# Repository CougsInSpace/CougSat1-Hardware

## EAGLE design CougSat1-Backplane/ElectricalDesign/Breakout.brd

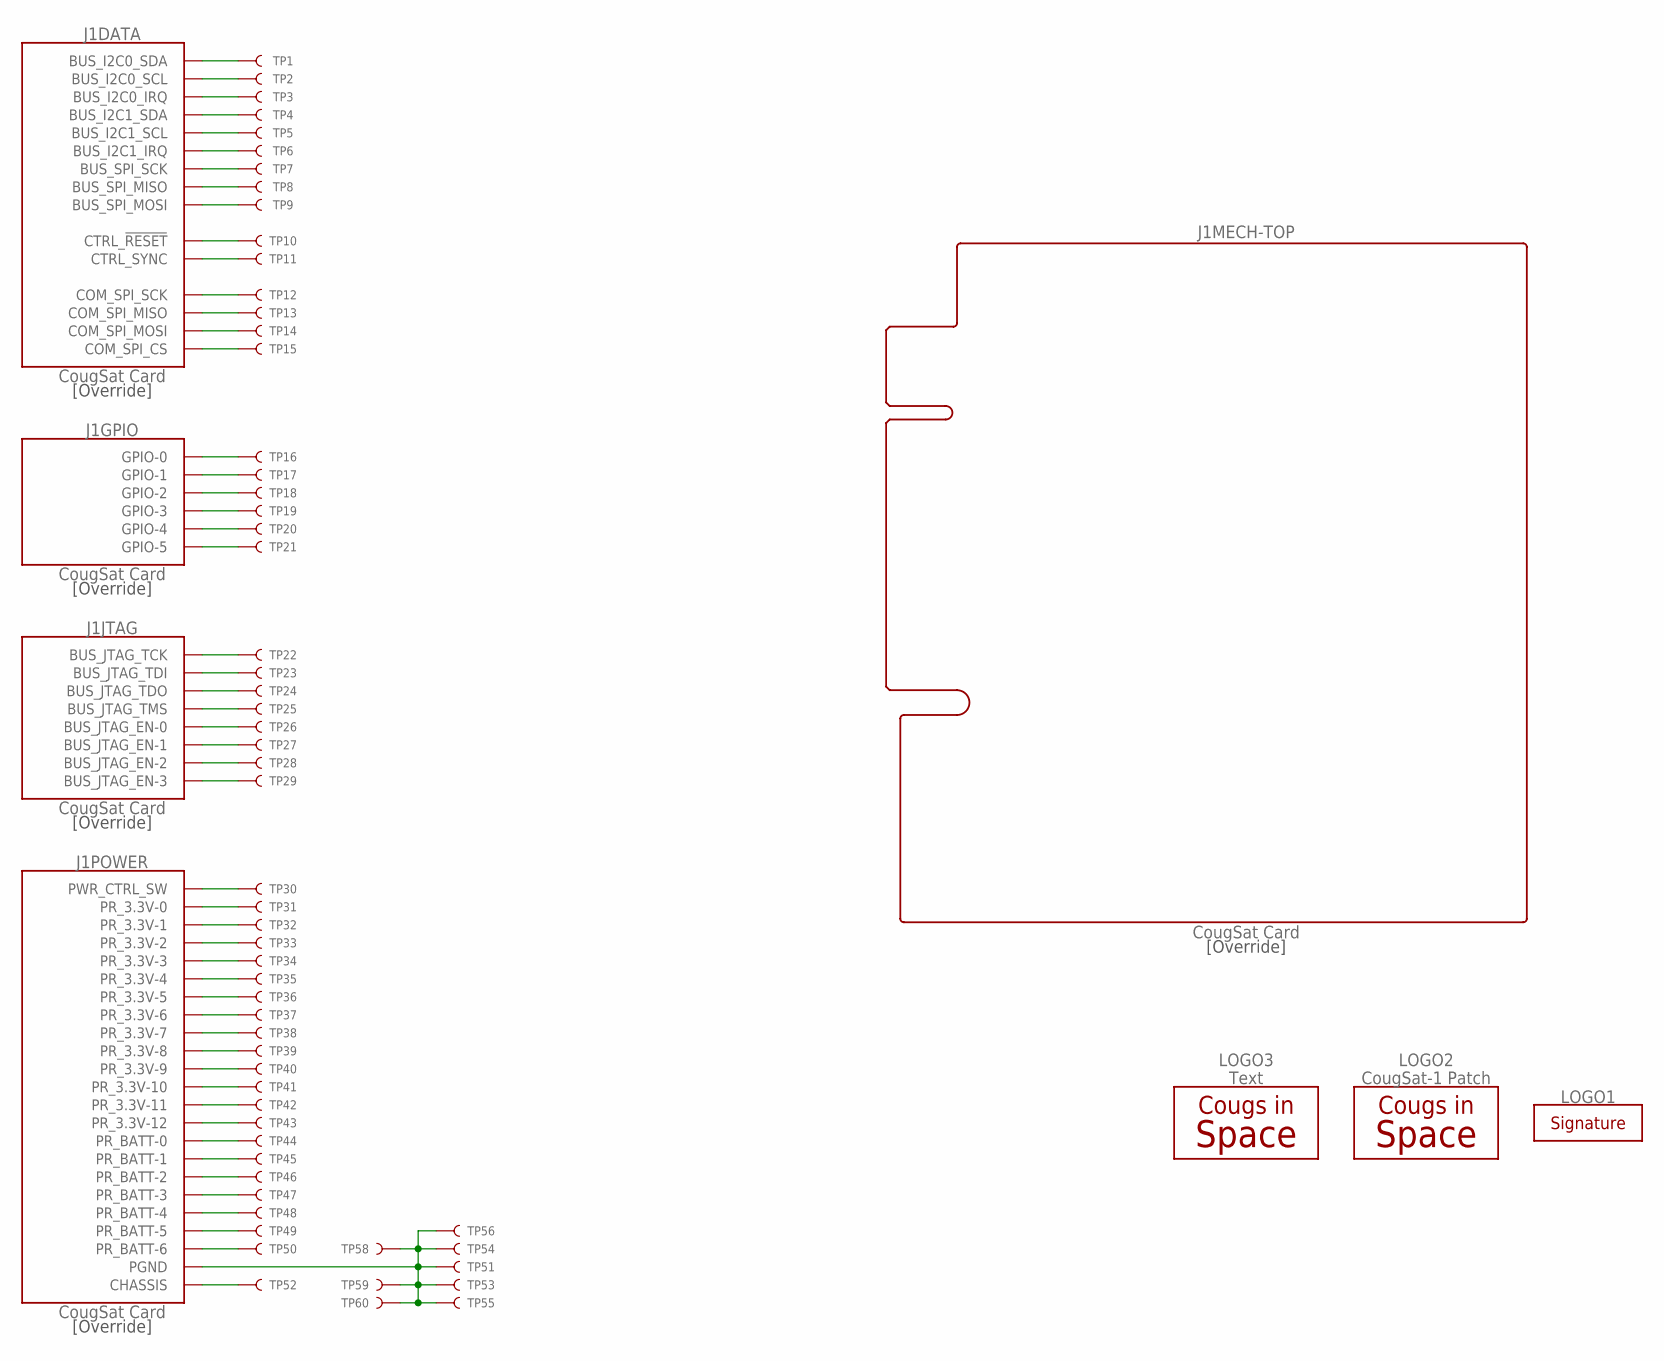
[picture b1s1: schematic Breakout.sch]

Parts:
J1: CougSat Card; CARD-FULL
LOGO1: SIGNATUREHENDRIK; SIGN-HENDRIK
LOGO2: CougSat-1 Patch; CIS-PATCH-1
LOGO3: Text; CIS-TEXT
TP1, TP2, TP3, TP4, TP5, TP6, TP7, TP8, TP9, TP10, TP11, TP12, TP13, TP14, TP15, TP16, TP17, TP18, TP19, TP20, TP21, TP22, TP23, TP24, TP25, TP26, TP27, TP28, TP29, TP30, TP31, TP32, TP33, TP34, TP35, TP36, TP37, TP38, TP39, TP40, TP41, TP42, TP43, TP44, TP45, TP46, TP47, TP48, TP49, TP50, TP51, TP52, TP53, TP54, TP55, TP56, TP58, TP59, TP60: TEST_POINT-THT-1.0; THT-1.0

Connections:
BUS_12C0_IRQ: J1.A45 (BUS_I2C0_IRQ), J1.B45 (BUS_I2C0_IRQ), TP3.1
BUS_12C0_SCL: J1.A44 (BUS_I2C0_SCL), J1.B44 (BUS_I2C0_SCL), TP2.1
BUS_12C0_SDA: J1.A43 (BUS_I2C0_SDA), J1.B43 (BUS_I2C0_SDA), TP1.1
BUS_12C1_IRQ: J1.A32 (BUS_I2C1_IRQ), J1.B32 (BUS_I2C1_IRQ), TP6.1
BUS_12C1_SCL: J1.A31 (BUS_I2C1_SCL), J1.B31 (BUS_I2C1_SCL), TP5.1
BUS_12C1_SDA: J1.A30 (BUS_I2C1_SDA), J1.B30 (BUS_I2C1_SDA), TP4.1
BUS_JTAG_EN-0: J1.B46 (BUS_JTAG_EN-0), TP26.1
BUS_JTAG_EN-1: J1.B47 (BUS_JTAG_EN-1), TP27.1
BUS_JTAG_EN-2: J1.B48 (BUS_JTAG_EN-2), TP28.1
BUS_JTAG_EN-3: J1.B49 (BUS_JTAG_EN-3), TP29.1
BUS_JTAG_TCK: J1.A46 (BUS_JTAG_TCK), TP22.1
BUS_JTAG_TDI: J1.A47 (BUS_JTAG_TDI), TP23.1
BUS_JTAG_TDO: J1.A48 (BUS_JTAG_TDO), TP24.1
BUS_JTAG_TMS: J1.A49 (BUS_JTAG_TMS), TP25.1
BUS_SPI_MISO: J1.A38 (BUS_SPI_MISO), J1.B38 (BUS_SPI_MISO), TP8.1
BUS_SPI_MOSI: J1.A39 (BUS_SPI_MOSI), J1.B39 (BUS_SPI_MOSI), TP9.1
BUS_SPI_SCK: J1.A37 (BUS_SPI_SCK), J1.B37 (BUS_SPI_SCK), TP7.1
CHASSIS: J1.CHASSIS@1 (CHASSIS), J1.CHASSIS@2 (CHASSIS), J1.CHASSIS@3 (CHASSIS), J1.CHASSIS@4 (CHASSIS), TP52.1
COM_SPI_CS: J1.A36 (COM_SPI_CS), J1.B36 (COM_SPI_CS), TP15.1
COM_SPI_MISO: J1.A34 (COM_SPI_MISO), J1.B34 (COM_SPI_MISO), TP13.1
COM_SPI_MOSI: J1.A35 (COM_SPI_MOSI), J1.B35 (COM_SPI_MOSI), TP14.1
COM_SPI_SCK: J1.A33 (COM_SPI_SCK), J1.B33 (COM_SPI_SCK), TP12.1
CTRL_RESET: J1.A41 (CTRL_!RESET), J1.B41 (CTRL_!RESET), TP10.1
CTRL_SYNC: J1.A42 (CTRL_SYNC), J1.B42 (CTRL_SYNC), TP11.1
GPIO-0: J1.A24 (GPIO-0), TP16.1
GPIO-1: J1.A25 (GPIO-1), TP17.1
GPIO-2: J1.A26 (GPIO-2), TP18.1
GPIO-3: J1.A27 (GPIO-3), TP19.1
GPIO-4: J1.A28 (GPIO-4), TP20.1
GPIO-5: J1.A29 (GPIO-5), TP21.1
PGND: J1.A21 (PGND), J1.A22 (PGND), J1.A23 (PGND), J1.B21 (PGND), J1.B22 (PGND), J1.B23 (PGND), J1.B24 (PGND), J1.B25 (PGND), J1.B26 (PGND), J1.B27 (PGND), J1.B28 (PGND), J1.B29 (PGND), TP51.1, TP53.1, TP54.1, TP55.1, TP56.1, TP58.1, TP59.1, TP60.1
PR_3.3V-0: J1.A1 (PR_3.3V-0), J1.B1 (PR_3.3V-0), TP31.1
PR_3.3V-1: J1.A2 (PR_3.3V-1), J1.B2 (PR_3.3V-1), TP32.1
PR_3.3V-2: J1.A3 (PR_3.3V-2), J1.B3 (PR_3.3V-2), TP33.1
PR_3.3V-3: J1.A4 (PR_3.3V-3), J1.B4 (PR_3.3V-3), TP34.1
PR_3.3V-4: J1.A5 (PR_3.3V-4), J1.B5 (PR_3.3V-4), TP35.1
PR_3.3V-5: J1.A6 (PR_3.3V-5), J1.B6 (PR_3.3V-5), TP36.1
PR_3.3V-6: J1.A7 (PR_3.3V-6), J1.B7 (PR_3.3V-6), TP37.1
PR_3.3V-7: J1.A8 (PR_3.3V-7), J1.B8 (PR_3.3V-7), TP38.1
PR_3.3V-8: J1.A9 (PR_3.3V-8), J1.B9 (PR_3.3V-8), TP39.1
PR_3.3V-9: J1.A10 (PR_3.3V-9), J1.B10 (PR_3.3V-9), TP40.1
PR_3.3V-10: J1.A11 (PR_3.3V-10), J1.B11 (PR_3.3V-10), TP41.1
PR_3.3V-11: J1.A12 (PR_3.3V-11), J1.B12 (PR_3.3V-11), TP42.1
PR_3.3V-12: J1.A13 (PR_3.3V-12), J1.B13 (PR_3.3V-12), TP43.1
PR_BATT-0: J1.A14 (PR_BATT-0), J1.B14 (PR_BATT-0), TP44.1
PR_BATT-1: J1.A15 (PR_BATT-1), J1.B15 (PR_BATT-1), TP45.1
PR_BATT-2: J1.A16 (PR_BATT-2), J1.B16 (PR_BATT-2), TP46.1
PR_BATT-3: J1.A17 (PR_BATT-3), J1.B17 (PR_BATT-3), TP47.1
PR_BATT-4: J1.A18 (PR_BATT-4), J1.B18 (PR_BATT-4), TP48.1
PR_BATT-5: J1.A19 (PR_BATT-5), J1.B19 (PR_BATT-5), TP49.1
PR_BATT-6: J1.A20 (PR_BATT-6), J1.B20 (PR_BATT-6), TP50.1
PWR_CTRL_SW: J1.A40 (PWR_CTRL_SW), J1.B40 (PWR_CTRL_SW), TP30.1

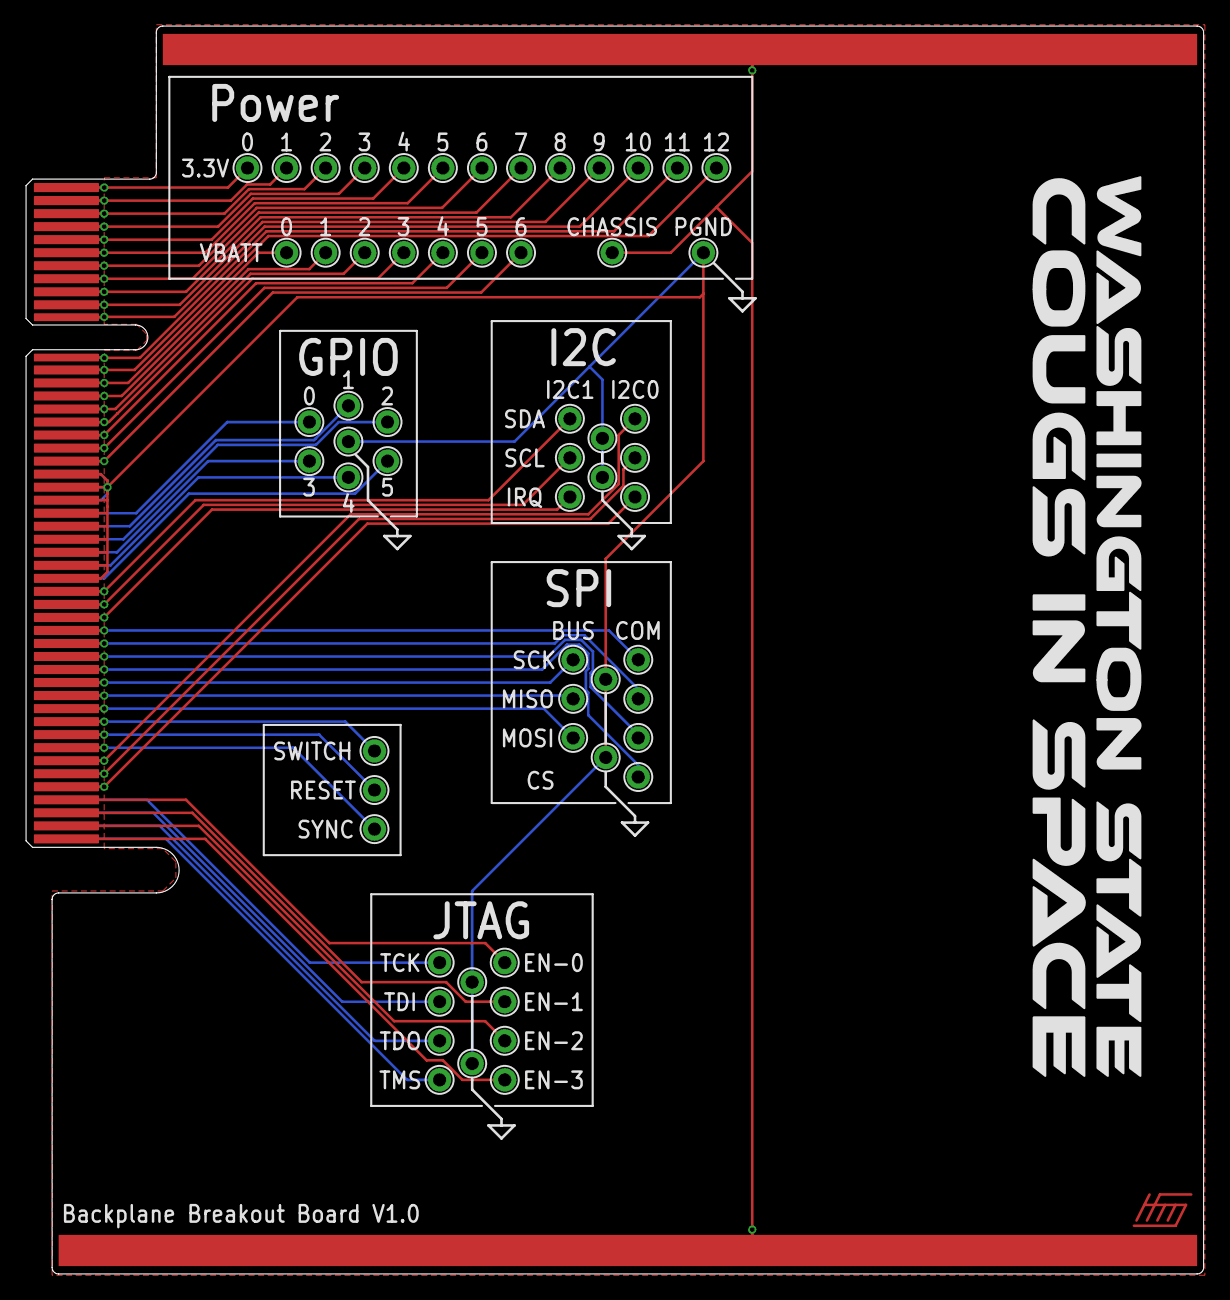
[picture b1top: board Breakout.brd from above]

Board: 2 copper layers, 90.4 x 95.8 mm, 63 parts (1 on the bottom side), 52 nets.

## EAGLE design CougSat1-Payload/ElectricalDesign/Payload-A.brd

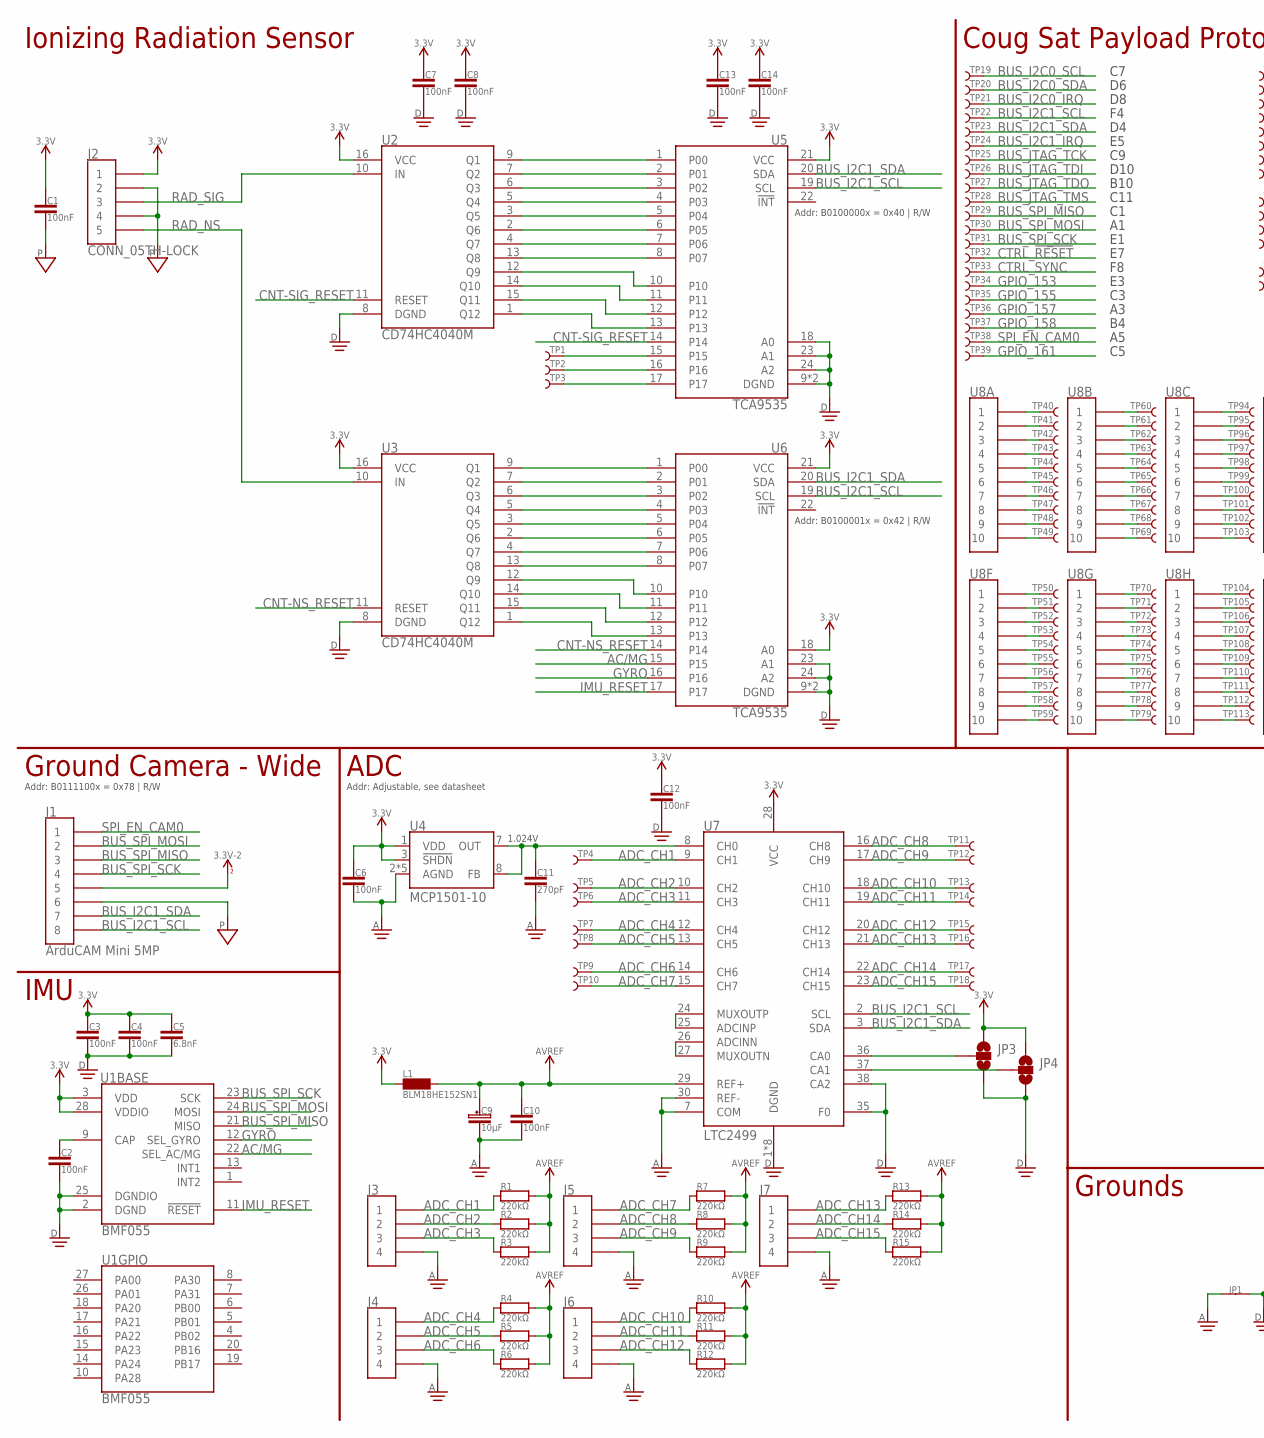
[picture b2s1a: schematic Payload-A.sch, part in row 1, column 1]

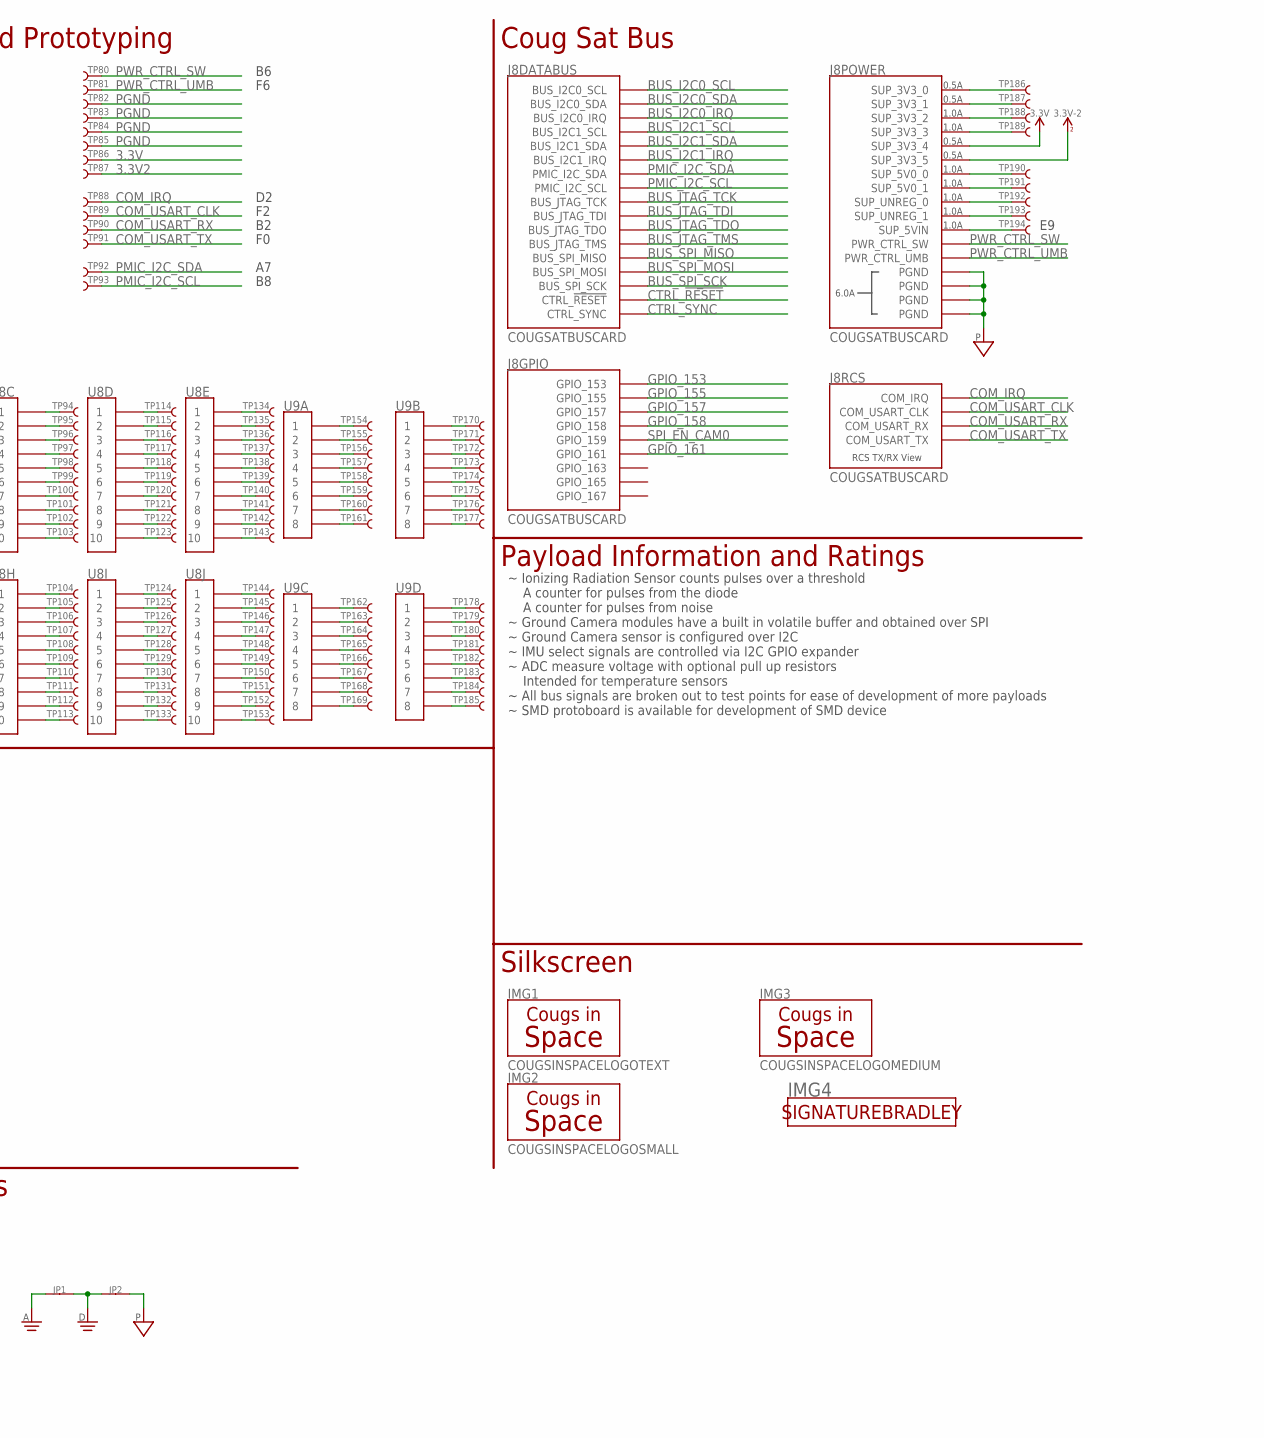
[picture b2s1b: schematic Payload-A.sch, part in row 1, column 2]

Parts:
C1, C2, C3, C4, C6, C7, C8, C10, C13, C14: 100nF; 1608
C5: 6.8nF; 1608
C9: 10µF; 4028-POL
C11: 270pF; 1608
C12: 100nF; 3216
IMG1: COUGSINSPACELOGOTEXT; COUGSINSPACETEXT
IMG2: COUGSINSPACELOGOSMALL; COUGSINSPACELOGO_SMALL
IMG3: COUGSINSPACELOGOMEDIUM; COUGSINSPACELOGO_MEDIUM
IMG4: SIGNATUREBRADLEY; SIGNATURE-BRADLEY
J1: ArduCAM Mini 5MP; 1X08_LOCK
J2: CONN_05TH-LOCK; 1X05_LOCK
J3, J4, J5, J6, J7: CONN_04PICOLOCK1.5MM; 1X04_PICOLOCK1.5MM
J8: COUGSATBUSCARD; COUGSATBUS_MALE-SODIMM
JP1, JP2: SHORTCIRCUIT1608JUMPER; 1608
JP3, JP4: JUMPER-SMT_3_NO_SILK; SMT-JUMPER_3_NO_SILK
L1: BLM18HE152SN1; 1608
R1, R2, R3, R4, R5, R6, R7, R8, R9, R10, R11, R12, R13, R14, R15: 220kΩ; 1608
TP1, TP2, TP3, TP4, TP5, TP6, TP7, TP8, TP9, TP10, TP11, TP12, TP13, TP14, TP15, TP16, TP17, TP18, TP19, TP20, TP21, TP22, TP23, TP24, TP25, TP26, TP27, TP28, TP29, TP30, TP31, TP32, TP33, TP34, TP35, TP36, TP37, TP38, TP39, TP80, TP81, TP82, TP83, TP84, TP85, TP86, TP87, TP88, TP89, TP90, TP91, TP92, TP93, TP186, TP187, TP188, TP189, TP190, TP191, TP192, TP193, TP194: TEST-POINT1.25MM; PAD1.25X1.25
TP40, TP41, TP42, TP43, TP44, TP45, TP46, TP47, TP48, TP49, TP50, TP51, TP52, TP53, TP54, TP55, TP56, TP57, TP58, TP59, TP60, TP61, TP62, TP63, TP64, TP65, TP66, TP67, TP68, TP69, TP70, TP71, TP72, TP73, TP74, TP75, TP76, TP77, TP78, TP79, TP94, TP95, TP96, TP97, TP98, TP99, TP100, TP101, TP102, TP103, TP104, TP105, TP106, TP107, TP108, TP109, TP110, TP111, TP112, TP113, TP114, TP115, TP116, TP117, TP118, TP119, TP120, TP121, TP122, TP123, TP124, TP125, TP126, TP127, TP128, TP129, TP130, TP131, TP132, TP133, TP134, TP135, TP136, TP137, TP138, TP139, TP140, TP141, TP142, TP143, TP144, TP145, TP146, TP147, TP148, TP149, TP150, TP151, TP152, TP153, TP154, TP155, TP156, TP157, TP158, TP159, TP160, TP161, TP162, TP163, TP164, TP165, TP166, TP167, TP168, TP169, TP170, TP171, TP172, TP173, TP174, TP175, TP176, TP177, TP178, TP179, TP180, TP181, TP182, TP183, TP184, TP185: TEST-POINT1MM; PAD1X1
U1: BMF055; LGA28-4X5MM
U2, U3: CD74HC4040M; SO16
U4: MCP1501-10; WDFN8-2X2
U5, U6: TCA9535; QFN24-4X4
U7: LTC2499; QFN38-5X7
U8: PROTOBOARD-100SMD0.5MM; PROTOBOARD-SMD0.5MM
U9: PROTOBOARD-32SOIC; PROTOBOARD-SOIC

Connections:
3.3V: C1.1, C3.1, C4.1, C5.1, C6.1, C7.1, C8.1, C12.1, C13.1, C14.1, J2.1, J8.42 (SUP_3V3_4), J8.44 (SUP_3V3_4), J8.46 (SUP_3V3_4), J8.48 (SUP_3V3_4), J8.50 (SUP_3V3_4), JP3.1, JP4.1, L1.2, TP86.1, U1.3 (VDD), U1.28 (VDDIO), U2.16 (VCC), U3.16 (VCC), U4.1 (VDD), U4.3 (!SHDN), U5.21 (VCC), U6.18 (A0), U6.21 (VCC), U7.28 (VCC)
3.3V2: J1.5, J8.52 (SUP_3V3_5), J8.54 (SUP_3V3_5), J8.56 (SUP_3V3_5), J8.58 (SUP_3V3_5), J8.60 (SUP_3V3_5), TP87.1
AC/MG: U1.22 (SEL_AC/MG), U6.15
ADCS_ADCINP: U7.24 (MUXOUTP), U7.25 (ADCINP)
ADCS_ADCSINN: U7.26 (ADCINN), U7.27 (MUXOUTN)
ADC_CA0: JP3.2, U7.36 (CA0)
ADC_CA1: JP4.2, U7.37 (CA1)
ADC_CH1: J3.1, R1.1, TP4.1, U7.9 (CH1)
ADC_CH2: J3.2, R2.1, TP5.1, U7.10 (CH2)
ADC_CH3: J3.3, R3.1, TP6.1, U7.11 (CH3)
ADC_CH4: J4.1, R4.1, TP7.1, U7.12 (CH4)
ADC_CH5: J4.2, R5.1, TP8.1, U7.13 (CH5)
ADC_CH6: J4.3, R6.1, TP9.1, U7.14 (CH6)
ADC_CH7: J5.1, R7.1, TP10.1, U7.15 (CH7)
ADC_CH8: J5.2, R8.1, TP11.1, U7.16 (CH8)
ADC_CH9: J5.3, R9.1, TP12.1, U7.17 (CH9)
ADC_CH10: J6.1, R10.1, TP13.1, U7.18 (CH10)
ADC_CH11: J6.2, R11.1, TP14.1, U7.19 (CH11)
ADC_CH12: J6.3, R12.1, TP15.1, U7.20 (CH12)
ADC_CH13: J7.1, R13.1, TP16.1, U7.21 (CH13)
ADC_CH14: J7.2, R14.1, TP17.1, U7.22 (CH14)
ADC_CH15: J7.3, R15.1, TP18.1, U7.23 (CH15)
ADC_VREF_ICOUT: C11.1, U4.7 (OUT), U4.8 (FB), U7.8 (CH0)
AGND: C6.2, C9.C, C10.2, C11.2, J3.4, J4.4, J5.4, J6.4, J7.4, JP1.1, U4.2 (AGND), U4.4 (AGND), U4.5 (AGND), U4.6 (AGND), U4.PAD (AGND), U7.7 (COM), U7.30 (REF-)
AVREF: C9.A, C10.1, L1.1, R1.2, R2.2, R3.2, R4.2, R5.2, R6.2, R7.2, R8.2, R9.2, R10.2, R11.2, R12.2, R13.2, R14.2, R15.2, U7.29 (REF+)
BUS_I2C0_IRQ: J8.177 (BUS_I2C0_IRQ), J8.179 (BUS_I2C0_IRQ), TP21.1
BUS_I2C0_SCL: J8.173 (BUS_I2C0_SCL), J8.175 (BUS_I2C0_SCL), TP19.1
BUS_I2C0_SDA: J8.169 (BUS_I2C0_SDA), J8.171 (BUS_I2C0_SDA), TP20.1
BUS_I2C1_IRQ: J8.164 (BUS_I2C1_IRQ), TP24.1
BUS_I2C1_SCL: J1.8, J8.160 (BUS_I2C1_SCL), TP22.1, U5.19 (SCL), U6.19 (SCL), U7.2 (SCL)
BUS_I2C1_SDA: J1.7, J8.162 (BUS_I2C1_SDA), TP23.1, U5.20 (SDA), U6.20 (SDA), U7.3 (SDA)
BUS_JTAG_TCK: J8.185 (BUS_JTAG_TCK), J8.187 (BUS_JTAG_TCK), TP25.1
BUS_JTAG_TDI: J8.189 (BUS_JTAG_TDI), J8.191 (BUS_JTAG_TDI), TP26.1
BUS_JTAG_TDO: J8.193 (BUS_JTAG_TDO), J8.195 (BUS_JTAG_TDO), TP27.1
BUS_JTAG_TMS: J8.197 (BUS_JTAG_TMS), J8.199 (BUS_JTAG_TMS), TP28.1
BUS_SPI_MISO: J1.3, J8.145 (BUS_SPI_MISO), J8.147 (BUS_SPI_MISO), TP29.1, U1.21 (MISO)
BUS_SPI_MOSI: J1.2, J8.149 (BUS_SPI_MOSI), J8.151 (BUS_SPI_MOSI), TP30.1, U1.24 (MOSI)
BUS_SPI_SCK: J1.4, J8.141 (BUS_SPI_SCK), J8.143 (BUS_SPI_SCK), TP31.1, U1.23 (SCK)
CNT-NS_1: U3.9 (Q1), U6.1 (P00)
CNT-NS_2: U3.7 (Q2), U6.2 (P01)
CNT-NS_3: U3.6 (Q3), U6.3 (P02)
CNT-NS_4: U3.5 (Q4), U6.4 (P03)
CNT-NS_5: U3.3 (Q5), U6.5 (P04)
CNT-NS_6: U3.2 (Q6), U6.6 (P05)
CNT-NS_7: U3.4 (Q7), U6.7 (P06)
CNT-NS_8: U3.13 (Q8), U6.8 (P07)
CNT-NS_9: U3.12 (Q9), U6.10
CNT-NS_10: U3.14 (Q10), U6.11
CNT-NS_11: U3.15 (Q11), U6.12
CNT-NS_12: U3.1 (Q12), U6.13
CNT-NS_RESET: U3.11 (RESET), U6.14
CNT-SIG_1: U2.9 (Q1), U5.1 (P00)
CNT-SIG_2: U2.7 (Q2), U5.2 (P01)
CNT-SIG_3: U2.6 (Q3), U5.3 (P02)
CNT-SIG_4: U2.5 (Q4), U5.4 (P03)
CNT-SIG_5: U2.3 (Q5), U5.5 (P04)
CNT-SIG_6: U2.2 (Q6), U5.6 (P05)
CNT-SIG_7: U2.4 (Q7), U5.7 (P06)
CNT-SIG_8: U2.13 (Q8), U5.8 (P07)
CNT-SIG_9: U2.12 (Q9), U5.10
CNT-SIG_10: U2.14 (Q10), U5.11
CNT-SIG_11: U2.15 (Q11), U5.12
CNT-SIG_12: U2.1 (Q12), U5.13
CNT-SIG_RESET: U2.11 (RESET), U5.14
COM_IRQ: J8.154 (COM_IRQ), J8.156 (COM_IRQ), TP88.1
COM_USART_CLK: J8.150 (COM_USART_CLK), J8.152 (COM_USART_CLK), TP89.1
COM_USART_RX: J8.146 (COM_USART_RX), J8.148 (COM_USART_RX), TP90.1
COM_USART_TX: J8.142 (COM_USART_TX), J8.144 (COM_USART_TX), TP91.1
CTRL_!RESET: J8.174 (CTRL_!RESET), J8.176 (CTRL_!RESET), TP32.1
CTRL_SYNC: J8.178 (CTRL_SYNC), J8.180 (CTRL_SYNC), TP33.1
DGND: C2.2, C3.2, C4.2, C5.2, C7.2, C8.2, C12.2, C13.2, C14.2, JP1.2, JP2.1, JP3.3, JP4.3, U1.2 (DGND), U1.25 (DGNDIO), U2.8 (DGND), U3.8 (DGND), U5.9 (DGND), U5.18 (A0), U5.23 (A1), U5.24 (A2), U5.PAD (DGND), U6.9 (DGND), U6.23 (A1), U6.24 (A2), U6.PAD (DGND), U7.1 (DGND), U7.4 (DGND), U7.6 (DGND), U7.31 (DGND), U7.32 (DGND), U7.33 (DGND), U7.34 (DGND), U7.35 (F0), U7.38 (CA2), U7.PAD (DGND)
GPIO_153: J8.153 (GPIO_153), TP34.1
GPIO_155: J8.155 (GPIO_155), TP35.1
GPIO_157: J8.157 (GPIO_157), TP36.1
GPIO_158: J8.158 (GPIO_158), TP37.1
GPIO_161: J8.161 (GPIO_161), TP39.1
GPIO_P15: TP1.1, U5.15
GPIO_P16: TP2.1, U5.16
GPIO_P17: TP3.1, U5.17
GYRO: U1.12 (SEL_GYRO), U6.16
IMU2_CAP: C2.1, U1.9 (CAP)
IMU_RESET: U1.11 (!RESET), U6.17
PGND: C1.2, J1.6, J2.2, J2.4, J8.1 (PGND), J8.3 (PGND), J8.5 (PGND), J8.7 (PGND), J8.9 (PGND), J8.11 (PGND), J8.13 (PGND), J8.15 (PGND), J8.17 (PGND), J8.19 (PGND), J8.41 (PGND), J8.43 (PGND), J8.45 (PGND), J8.47 (PGND), J8.49 (PGND), J8.51 (PGND), J8.53 (PGND), J8.55 (PGND), J8.57 (PGND), J8.59 (PGND), J8.61 (PGND), J8.63 (PGND), J8.65 (PGND), J8.67 (PGND), J8.69 (PGND), J8.82 (PGND), J8.84 (PGND), J8.86 (PGND), J8.88 (PGND), J8.90 (PGND), J8.92 (PGND), J8.94 (PGND), J8.96 (PGND), J8.98 (PGND), J8.100 (PGND), J8.102 (PGND), J8.104 (PGND), J8.106 (PGND), J8.108 (PGND), J8.110 (PGND), J8.112 (PGND), J8.114 (PGND), J8.116 (PGND), J8.118 (PGND), J8.120 (PGND), J8.122 (PGND), J8.124 (PGND), J8.126 (PGND), J8.128 (PGND), J8.130 (PGND), J8.131 (PGND), J8.132 (PGND), J8.133 (PGND), J8.134 (PGND), J8.135 (PGND), J8.136 (PGND), J8.137 (PGND), J8.138 (PGND), J8.139 (PGND), J8.140 (PGND), JP2.2, TP82.1, TP83.1, TP84.1, TP85.1
PMIC_I2C_SCL: J8.183 (PMIC_I2C_SCL), TP93.1
PMIC_I2C_SDA: J8.181 (PMIC_I2C_SDA), TP92.1
PWR_CTRL_SW: J8.166 (PWR_CTRL_SW), J8.168 (PWR_CTRL_SW), TP80.1
PWR_CTRL_UMB: J8.170 (PWR_CTRL_UMB), J8.172 (PWR_CTRL_UMB), TP81.1
RAD_NS: J2.5, U3.10 (IN)
RAD_SIG: J2.3, U2.10 (IN)
SMD0.5-1: TP40.1, U8.1
SMD0.5-2: TP41.1, U8.2
SMD0.5-3: TP42.1, U8.3
SMD0.5-4: TP43.1, U8.4
SMD0.5-5: TP44.1, U8.5
SMD0.5-6: TP45.1, U8.6
SMD0.5-7: TP46.1, U8.7
SMD0.5-8: TP47.1, U8.8
SMD0.5-9: TP48.1, U8.9
SMD0.5-10: TP49.1, U8.10
SMD0.5-11: TP60.1, U8.11 (1)
SMD0.5-12: TP61.1, U8.12 (2)
SMD0.5-13: TP62.1, U8.13 (3)
SMD0.5-14: TP63.1, U8.14 (4)
SMD0.5-15: TP64.1, U8.15 (5)
SMD0.5-16: TP65.1, U8.16 (6)
SMD0.5-17: TP66.1, U8.17 (7)
SMD0.5-18: TP67.1, U8.18 (8)
SMD0.5-19: TP68.1, U8.19 (9)
SMD0.5-20: TP69.1, U8.20 (10)
SMD0.5-21: TP94.1, U8.21 (1)
SMD0.5-22: TP95.1, U8.22 (2)
SMD0.5-23: TP96.1, U8.23 (3)
SMD0.5-24: TP97.1, U8.24 (4)
SMD0.5-25: TP98.1, U8.25 (5)
SMD0.5-26: TP99.1, U8.26 (6)
SMD0.5-27: TP100.1, U8.27 (7)
SMD0.5-28: TP101.1, U8.28 (8)
SMD0.5-29: TP102.1, U8.29 (9)
SMD0.5-30: TP103.1, U8.30 (10)
SMD0.5-31: TP114.1, U8.31 (1)
SMD0.5-32: TP115.1, U8.32 (2)
SMD0.5-33: TP116.1, U8.33 (3)
SMD0.5-34: TP117.1, U8.34 (4)
SMD0.5-35: TP118.1, U8.35 (5)
SMD0.5-36: TP119.1, U8.36 (6)
SMD0.5-37: TP120.1, U8.37 (7)
SMD0.5-38: TP121.1, U8.38 (8)
SMD0.5-39: TP122.1, U8.39 (9)
SMD0.5-40: TP123.1, U8.40 (10)
SMD0.5-41: TP134.1, U8.41 (1)
SMD0.5-42: TP135.1, U8.42 (2)
SMD0.5-43: TP136.1, U8.43 (3)
SMD0.5-44: TP137.1, U8.44 (4)
SMD0.5-45: TP138.1, U8.45 (5)
SMD0.5-46: TP139.1, U8.46 (6)
SMD0.5-47: TP140.1, U8.47 (7)
SMD0.5-48: TP141.1, U8.48 (8)
SMD0.5-49: TP142.1, U8.49 (9)
SMD0.5-50: TP143.1, U8.50 (10)
SMD0.5-51: TP50.1, U8.51 (1)
SMD0.5-52: TP51.1, U8.52 (2)
SMD0.5-53: TP52.1, U8.53 (3)
SMD0.5-54: TP53.1, U8.54 (4)
SMD0.5-55: TP54.1, U8.55 (5)
SMD0.5-56: TP55.1, U8.56 (6)
SMD0.5-57: TP56.1, U8.57 (7)
SMD0.5-58: TP57.1, U8.58 (8)
SMD0.5-59: TP58.1, U8.59 (9)
SMD0.5-60: TP59.1, U8.60 (10)
SMD0.5-61: TP70.1, U8.61 (1)
SMD0.5-62: TP71.1, U8.62 (2)
SMD0.5-63: TP72.1, U8.63 (3)
SMD0.5-64: TP73.1, U8.64 (4)
SMD0.5-65: TP74.1, U8.65 (5)
SMD0.5-66: TP75.1, U8.66 (6)
SMD0.5-67: TP76.1, U8.67 (7)
SMD0.5-68: TP77.1, U8.68 (8)
SMD0.5-69: TP78.1, U8.69 (9)
SMD0.5-70: TP79.1, U8.70 (10)
SMD0.5-71: TP104.1, U8.71 (1)
SMD0.5-72: TP105.1, U8.72 (2)
SMD0.5-73: TP106.1, U8.73 (3)
SMD0.5-74: TP107.1, U8.74 (4)
SMD0.5-75: TP108.1, U8.75 (5)
SMD0.5-76: TP109.1, U8.76 (6)
SMD0.5-77: TP110.1, U8.77 (7)
SMD0.5-78: TP111.1, U8.78 (8)
SMD0.5-79: TP112.1, U8.79 (9)
SMD0.5-80: TP113.1, U8.80 (10)
SMD0.5-81: TP124.1, U8.81 (1)
SMD0.5-82: TP125.1, U8.82 (2)
SMD0.5-83: TP126.1, U8.83 (3)
SMD0.5-84: TP127.1, U8.84 (4)
SMD0.5-85: TP128.1, U8.85 (5)
SMD0.5-86: TP129.1, U8.86 (6)
SMD0.5-87: TP130.1, U8.87 (7)
SMD0.5-88: TP131.1, U8.88 (8)
SMD0.5-89: TP132.1, U8.89 (9)
SMD0.5-90: TP133.1, U8.90 (10)
SMD0.5-91: TP144.1, U8.91 (1)
SMD0.5-92: TP145.1, U8.92 (2)
SMD0.5-93: TP146.1, U8.93 (3)
SMD0.5-94: TP147.1, U8.94 (4)
SMD0.5-95: TP148.1, U8.95 (5)
SMD0.5-96: TP149.1, U8.96 (6)
SMD0.5-97: TP150.1, U8.97 (7)
SMD0.5-98: TP151.1, U8.98 (8)
SMD0.5-99: TP152.1, U8.99 (9)
SMD0.5-100: TP153.1, U8.100 (10)
SOIC-1: TP154.1, U9.1
SOIC-2: TP155.1, U9.2
SOIC-3: TP156.1, U9.3
SOIC-4: TP157.1, U9.4
SOIC-5: TP158.1, U9.5
SOIC-6: TP159.1, U9.6
SOIC-7: TP160.1, U9.7
SOIC-8: TP161.1, U9.8
SOIC-9: TP170.1, U9.9 (1)
SOIC-10: TP171.1, U9.10 (2)
SOIC-11: TP172.1, U9.11 (3)
SOIC-12: TP173.1, U9.12 (4)
SOIC-13: TP174.1, U9.13 (5)
SOIC-14: TP175.1, U9.14 (6)
SOIC-15: TP176.1, U9.15 (7)
SOIC-16: TP177.1, U9.16 (8)
SOIC-17: TP162.1, U9.17 (1)
SOIC-18: TP163.1, U9.18 (2)
SOIC-19: TP164.1, U9.19 (3)
SOIC-20: TP165.1, U9.20 (4)
SOIC-21: TP166.1, U9.21 (5)
SOIC-22: TP167.1, U9.22 (6)
SOIC-23: TP168.1, U9.23 (7)
SOIC-24: TP169.1, U9.24 (8)
SOIC-25: TP178.1, U9.25 (1)
SOIC-26: TP179.1, U9.26 (2)
SOIC-27: TP180.1, U9.27 (3)
SOIC-28: TP181.1, U9.28 (4)
SOIC-29: TP182.1, U9.29 (5)
SOIC-30: TP183.1, U9.30 (6)
SOIC-31: TP184.1, U9.31 (7)
SOIC-32: TP185.1, U9.32 (8)
SPI_EN_CAM0: J1.1, J8.159 (GPIO_159), TP38.1
SUP_3V3_0: J8.2 (SUP_3V3_0), J8.4 (SUP_3V3_0), J8.6 (SUP_3V3_0), J8.8 (SUP_3V3_0), J8.10 (SUP_3V3_0), TP186.1
SUP_3V3_1: J8.12 (SUP_3V3_1), J8.14 (SUP_3V3_1), J8.16 (SUP_3V3_1), J8.18 (SUP_3V3_1), J8.20 (SUP_3V3_1), TP187.1
SUP_3V3_2: J8.21 (SUP_3V3_2), J8.23 (SUP_3V3_2), J8.25 (SUP_3V3_2), J8.27 (SUP_3V3_2), J8.29 (SUP_3V3_2), J8.31 (SUP_3V3_2), J8.33 (SUP_3V3_2), J8.35 (SUP_3V3_2), J8.37 (SUP_3V3_2), J8.39 (SUP_3V3_2), TP188.1
SUP_3V3_3: J8.22 (SUP_3V3_3), J8.24 (SUP_3V3_3), J8.26 (SUP_3V3_3), J8.28 (SUP_3V3_3), J8.30 (SUP_3V3_3), J8.32 (SUP_3V3_3), J8.34 (SUP_3V3_3), J8.36 (SUP_3V3_3), J8.38 (SUP_3V3_3), J8.40 (SUP_3V3_3), TP189.1
SUP_5V0_0: J8.62 (SUP_5V0_0), J8.64 (SUP_5V0_0), J8.66 (SUP_5V0_0), J8.68 (SUP_5V0_0), J8.70 (SUP_5V0_0), J8.72 (SUP_5V0_0), J8.74 (SUP_5V0_0), J8.76 (SUP_5V0_0), J8.78 (SUP_5V0_0), J8.80 (SUP_5V0_0), TP190.1
SUP_5V0_1: J8.71 (SUP_5V0_1), J8.73 (SUP_5V0_1), J8.75 (SUP_5V0_1), J8.77 (SUP_5V0_1), J8.79 (SUP_5V0_1), J8.81 (SUP_5V0_1), J8.83 (SUP_5V0_1), J8.85 (SUP_5V0_1), J8.87 (SUP_5V0_1), J8.89 (SUP_5V0_1), TP191.1
SUP_5VIN: J8.182 (SUP_5VIN), J8.184 (SUP_5VIN), J8.186 (SUP_5VIN), J8.188 (SUP_5VIN), J8.190 (SUP_5VIN), J8.192 (SUP_5VIN), J8.194 (SUP_5VIN), J8.196 (SUP_5VIN), J8.198 (SUP_5VIN), J8.200 (SUP_5VIN), TP194.1
SUP_UNREG_0: J8.91 (SUP_UNREG_0), J8.93 (SUP_UNREG_0), J8.95 (SUP_UNREG_0), J8.97 (SUP_UNREG_0), J8.99 (SUP_UNREG_0), J8.101 (SUP_UNREG_0), J8.103 (SUP_UNREG_0), J8.105 (SUP_UNREG_0), J8.107 (SUP_UNREG_0), J8.109 (SUP_UNREG_0), TP192.1
SUP_UNREG_1: J8.111 (SUP_UNREG_1), J8.113 (SUP_UNREG_1), J8.115 (SUP_UNREG_1), J8.117 (SUP_UNREG_1), J8.119 (SUP_UNREG_1), J8.121 (SUP_UNREG_1), J8.123 (SUP_UNREG_1), J8.125 (SUP_UNREG_1), J8.127 (SUP_UNREG_1), J8.129 (SUP_UNREG_1), TP193.1

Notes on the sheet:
Ionizing Radiation Sensor
Addr: B0100000x = 0x40 | R/W
Addr: B0100001x = 0x42 | R/W
Ground Camera - Wide
Addr: B0111100x = 0x78 | R/W
Coug Sat Bus
Payload Information and Ratings
~ Ionizing Radiation Sensor counts pulses over a threshold A counter for pulses from the diode A counter for pulses from noise ~ Ground Camera modules have a built in volatile buffer and obtained over SPI ~ Ground Camera sensor is configured over I2C ~ IMU select signals are controlled via I2C GPIO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
Coug Sat Payload Prototyping
IMU
ADC
1.024V
Addr: Adjustable, see datasheet
Grounds
Silkscreen
B10
D10
C11

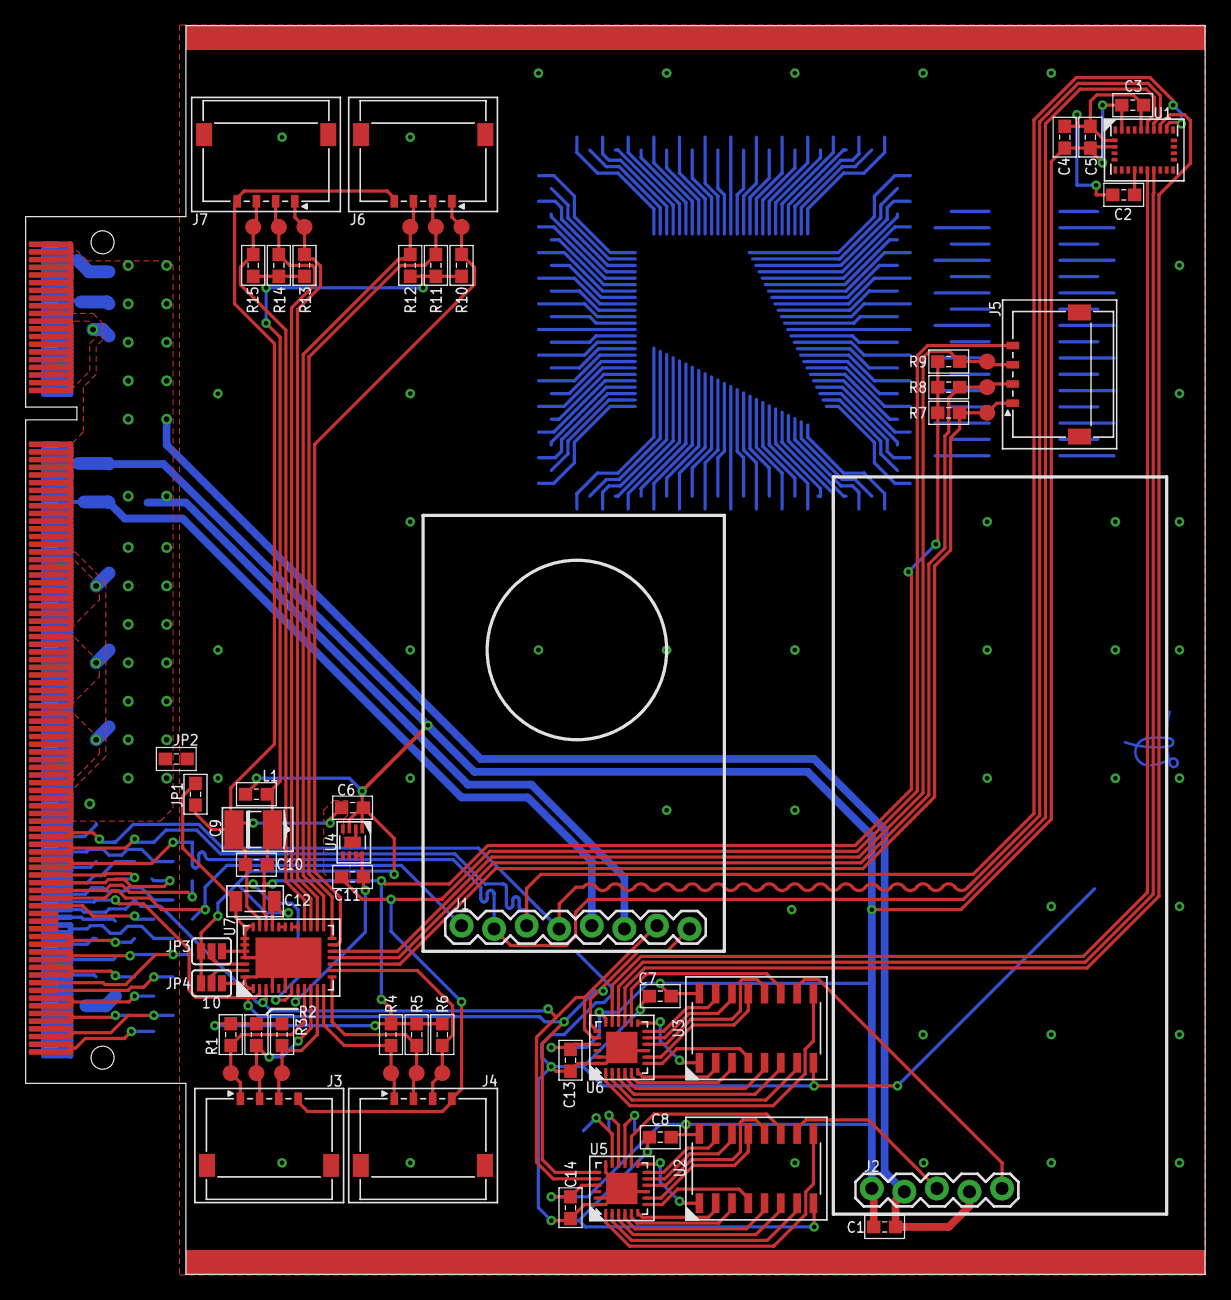
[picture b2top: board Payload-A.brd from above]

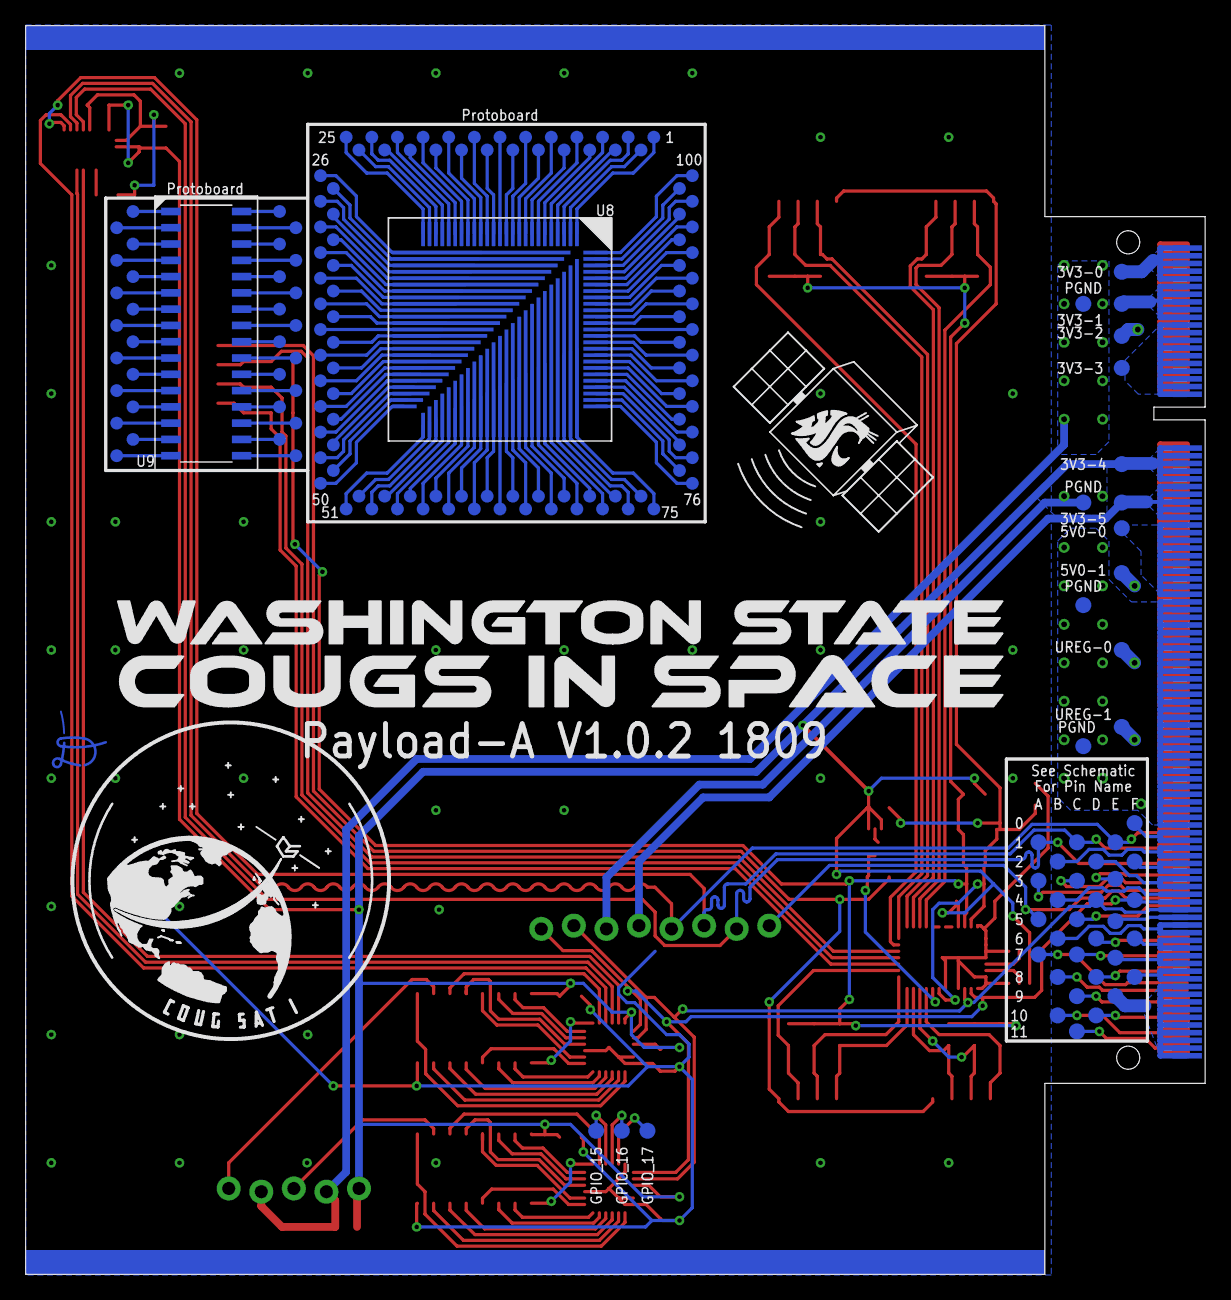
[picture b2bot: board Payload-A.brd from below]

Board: 2 copper layers, 92.0 x 97.4 mm, 249 parts (185 on the bottom side), 231 nets.

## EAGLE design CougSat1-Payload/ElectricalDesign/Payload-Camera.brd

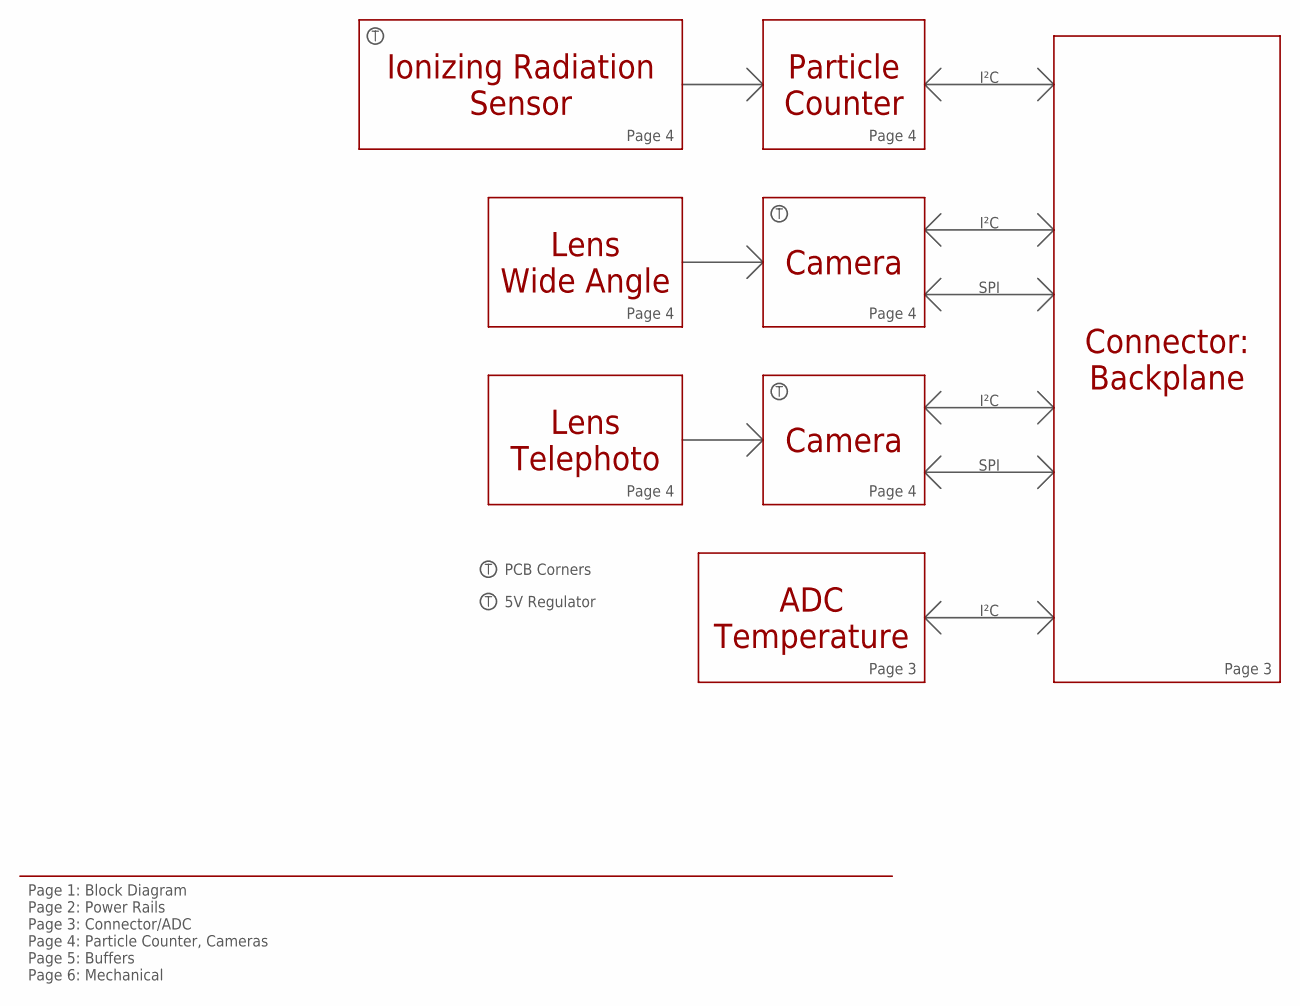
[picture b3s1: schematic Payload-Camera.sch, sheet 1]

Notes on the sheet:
Connector: Backplane
Camera
Lens Wide Angle
Lens Telephoto
Ionizing Radiation Sensor
Particle Counter
ADC Temperature
I²C
SPI
PCB Corners
Page 1: Block Diagram Page 2: Power Rails Page 3: Connector/ADC Page 4: Particle Counter, Cameras Page 5: Buffers Page 6: Mechanical
Page 4
Page 3
5V Regulator
